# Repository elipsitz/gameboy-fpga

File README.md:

# FPGA Game Boy Emulator

This repository contains a Game Boy / Game Boy Color emulator, written in [Chisel](https://www.chisel-lang.org/), that can be run on an FPGA. Read the full writeup [here](https://eli.lipsitz.net/posts/fpga-gameboy-emulator/).

Currently, only the Pynq-Z2 is supported, although the core of the emulator should be able to be used on any FPGA with sufficient resources.

## Building

A precompiled bitstream is available under Releases.

### Setup

#### Install Vivado

Currently this project uses Vivado 2020.2. The free edition is sufficient. Make sure to install with support for Zynq-7000 SoCs.

Install the [Pynq-Z2 Vivado board files](https://pynq.readthedocs.io/en/latest/overlay_design_methodology/board_settings.html).

Additionally, you should set up a shared IP cache to speed up synthesis of Xilinx IP:
1. Create the `~/vivado_ip_cache` directory (could be located somewhere else).
2. Create the file `~/.Xilinx/Vivado/Vivado_init.tcl`
3. In that file, add `set_param project.defaultIPCacheSetting /home/eli/vivado_ip_cache/` (substituting the absolute path to the IP cache directory).

#### Install other tools

You'll need to install JDK 8 or later, and [Scala Build Tool (`sbt`)](https://www.scala-sbt.org/download.html). Additionally, install [FuseSoC](https://github.com/olofk/fusesoc).

### Building the bitstream

From the top-level directory:

```
fusesoc --cores-root . run --build --target=pynq_z2 elipsitz:gameboy:gameboy
```

This will generate a `.bit` and `.hwh` file, which need to be accessible to the PS Python code.

## Running

### Setup

Install Pynq Linux on the Pynq-Z2, and install the pip packages listed in `python/requirements.txt`.

Transfer the `gameboy_ps` Python module (located in the `python` directory) to the Pynq-Z2.

Place the `gameboy.bit` and `gameboy.hwh` files from the build process in the `gameboy_ps/resources` directory.

### HDMI and Controller

Connect an HDMI cable from the "HDMI OUT" port on the Pynq-Z2 to a monitor or TV.

Attach an Xbox-compatible controller to the USB port of the Pynq-Z2.

### Running 

As root, run `python3 -m gameboy_ps <path to ROM directory>`, passing the path to the directory containing ROM files.

The program will load the bitstream to the PL. It takes a few seconds to load all of the Pynq libraries, but the main menu should soon show up on the display.

Warning: the audio output can be quite loud. Start at the lowest setting on the monitor/TV and increase it as needed.

## Building the cartridge adapter board

To play physical cartridges, you'll need to assemble the adapter board. KiCad board files can be found in the `pcb/pynq_adapter_rev2` directory. The schematic is pre-populated with LCSC part numbers for easy assembly at JLCPCB.

You'll need to add a few components yourself. These are all easy to solder:

* A 2x20 0.1mm female pin header (e.g. [this one](https://www.adafruit.com/product/2222)). These are used for Raspberry Pi HATs, so they're pretty easy to find.
* A SPDT slide switch such as the [EG1218](https://octopart.com/search?q=EG1218), or just a 1x3 strip of 0.1mm male pin header and a jumper.
* A GBA SP slot (such as [this one](https://handheldlegend.com/products/game-boy-cartridge-slot)). These can be found quite cheaply on eBay or Aliexpress as well. They're all pretty much the same.
* If desired, a GBA link port (e.g. [this one](https://handheldlegend.com/products/game-boy-advance-ext-link-port)). These can also be found easily from other sources.

The other parts are relatively small, so I don't recommend hand soldering the board. However, if you want to assemble the whole thing yourself, in addition to assorted resistors and capacitors, you'll also need:

* 6x [74LVC1T45DCK](https://octopart.com/search?q=74LVC1T45DCK) 1-bit level shifters.
* 2x [74LVCH16T245DGGR](https://octopart.com/search?q=74LVCH16T245DGGR) 16-bit level shifters. The non 'H' version should work as well, but the 'H' (bus hold) version is preferable.

## Appendix

### Getting Xbox controller to work on Pynq-Z2

This needs the `xpad` and `joydev` drivers. Pynq Linux isn't built with them. If you're running Pynq Linux with kernel `5.15.19-xilinx-v2022.1`, prebuilt kernel modules can be found in the `extra` directory in the repository. Otherwise, to build loadable kernel modules from scratch:

On the Pynq-Z2, go to `/lib/modules/5.15.19-xilinx-v2022.1/build`.

Download the right version of [`xpad.c`](https://raw.githubusercontent.com/torvalds/linux/v5.15/drivers/input/joystick/xpad.c)
to `drivers/input/joystick/xpad.c`.

And do the same with [`joydev.c`](https://raw.githubusercontent.com/torvalds/linux/v5.15/drivers/input/joydev.c), to `drivers/input/joydev.c`.

The build commands in `/lib/modules` need to run with `sudo` due to permissions issues.

Do `sudo make menuconfig` and set:

* `Device Drivers --> Input device support --> Joystick interface` to `M` (for 'module')
* `Device Drivers --> Input device support --> Joysticks/gamepads --> X-box Gamepad support` to `M` (for 'module')

Save and exit.

Then build the modules:

```
sudo make scripts
sudo make distclean
sudo make prepare
sudo make modules_prepare

sudo make -C . M=drivers/input/ joydev.ko
sudo make -C . M=drivers/input/joystick xpad.ko
```

Install the modules so that they'll be loaded automatically on boot.
Copy the `.ko` files to `/usr/lib/modules/$(uname -r)/kernel/`, and append
to `/etc/modules`:

```
joydev
xpad
```

Alternatively, use `insmod <modules>.ko` to load them once.

Make sure the `xilinx` user is in the group `input`:
`sudo usermod -a -G input xilinx` (and re-login)

Install the Python library with `sudo pip3 install xbox360controller`

Create the device nodes if needed: https://docs.kernel.org/input/joydev/joystick.html#device-nodes

```
cd /dev
rm js*
mkdir input
mknod input/js0 c 13 0
mknod input/js1 c 13 1
mknod input/js2 c 13 2
mknod input/js3 c 13 3
ln -s input/js0 js0
ln -s input/js1 js1
ln -s input/js2 js2
ln -s input/js3 js3
```

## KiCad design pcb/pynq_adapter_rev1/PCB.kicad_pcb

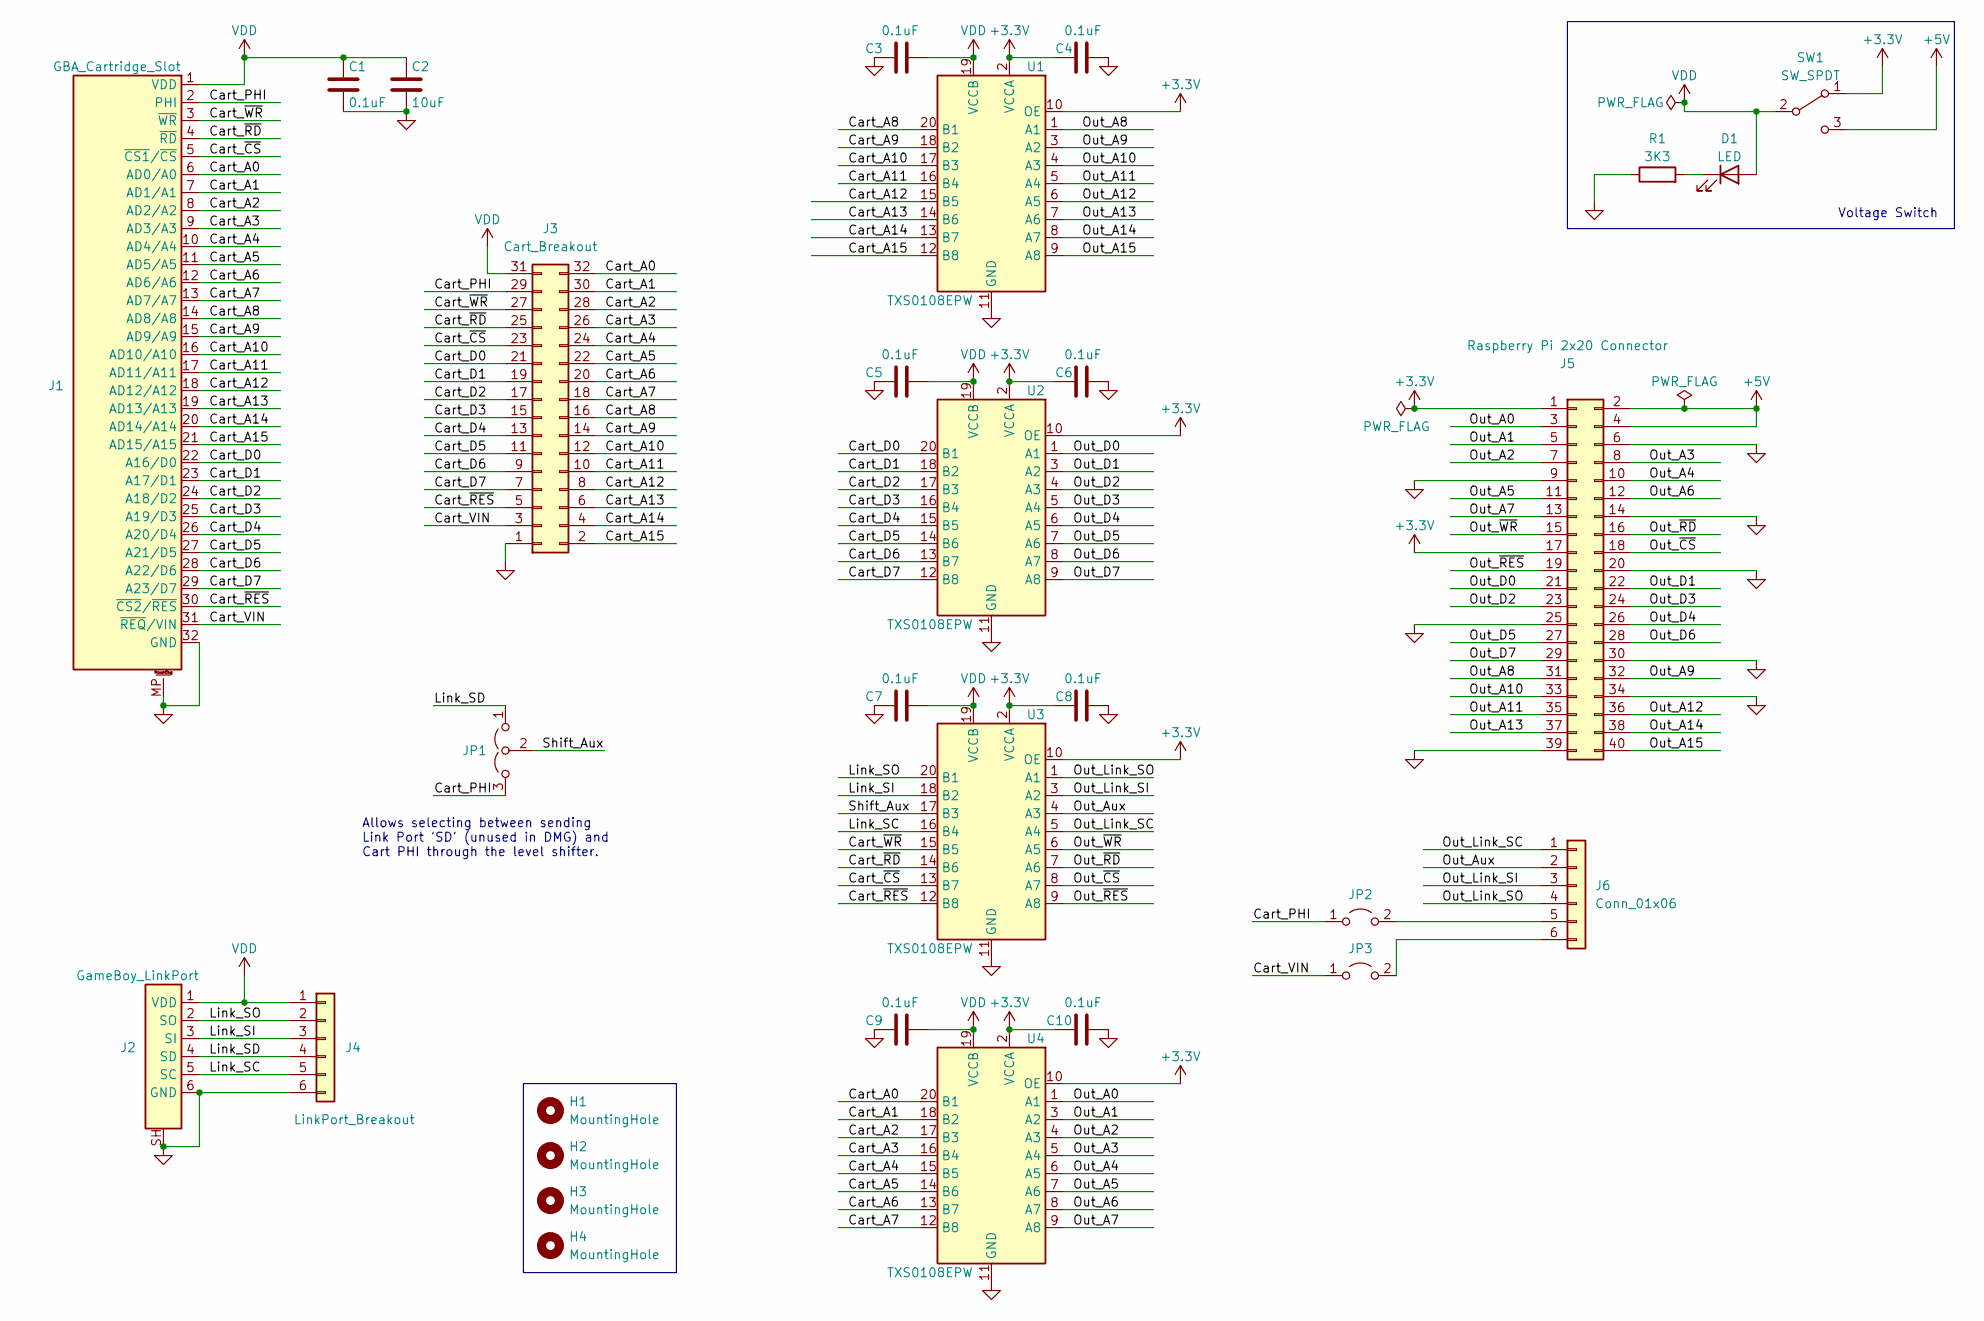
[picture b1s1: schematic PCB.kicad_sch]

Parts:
C1, C3, C4, C5, C6, C7, C8, C9, C10: 0.1uF; C_0603_1608Metric; LCSC C14663
C2: 10uF; C_1206_3216Metric; LCSC C13585
D1: LED; LED_0603_1608Metric; LCSC C2286
H1, H2, H3, H4: MountingHole; MountingHole_3.2mm_M3
J1: GBA_Cartridge_Slot; GameBoy_Cartridge_AGS_1x32-1MP_P1.50mm_Socket_Horizontal
J2: GameBoy_LinkPort; GameBoy_LinkPort_MGB_Horizontal
J3: Cart_Breakout; PinHeader_2x16_P2.54mm_Vertical
J4: LinkPort_Breakout; PinHeader_1x06_P2.54mm_Vertical
J5: Raspberry Pi 2x20 Connector; PinSocket_2x20_P2.54mm_Vertical
J6: Conn_01x06; PinHeader_1x06_P2.54mm_Vertical
JP1: Jumper_3_Open; PinHeader_1x03_P2.54mm_Vertical
JP2, JP3: Jumper_2_Open; PinHeader_1x02_P2.54mm_Vertical
R1: 3K3; R_0402_1005Metric; LCSC C25890
SW1: SW_SPDT; EG1218
U1, U2, U3, U4: TXS0108EPW; TSSOP-20_4.4x6.5mm_P0.65mm

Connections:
+3.3V: C4.2, C6.2, C8.2, C10.2, J5.1 (GND), J5.17 (3V3), SW1.1 (A), U1.2 (VCCA), U1.10 (OE), U2.2 (VCCA), U2.10 (OE), U3.2 (VCCA), U3.10 (OE), U4.2 (VCCA), U4.10 (OE)
+5V: J5.2 (5V), J5.4 (5V), SW1.3 (C)
/Cart_A0: J1.6 (AD0/A0), J3.32, U4.20 (B1)
/Cart_A1: J1.7 (AD1/A1), J3.30, U4.18 (B2)
/Cart_A2: J1.8 (AD2/A2), J3.28, U4.17 (B3)
/Cart_A3: J1.9 (AD3/A3), J3.26, U4.16 (B4)
/Cart_A4: J1.10 (AD4/A4), J3.24, U4.15 (B5)
/Cart_A5: J1.11 (AD5/A5), J3.22, U4.14 (B6)
/Cart_A6: J1.12 (AD6/A6), J3.20, U4.13 (B7)
/Cart_A7: J1.13 (AD7/A7), J3.18, U4.12 (B8)
/Cart_A8: J1.14 (AD8/A8), J3.16, U1.20 (B1)
/Cart_A9: J1.15 (AD9/A9), J3.14, U1.18 (B2)
/Cart_A10: J1.16 (AD10/A10), J3.12, U1.17 (B3)
/Cart_A11: J1.17 (AD11/A11), J3.10, U1.16 (B4)
/Cart_A12: J1.18 (AD12/A12), J3.8, U1.15 (B5)
/Cart_A13: J1.19 (AD13/A13), J3.6, U1.14 (B6)
/Cart_A14: J1.20 (AD14/A14), J3.4, U1.13 (B7)
/Cart_A15: J1.21 (AD15/A15), J3.2, U1.12 (B8)
/Cart_D0: J1.22 (A16/D0), J3.21, U2.20 (B1)
/Cart_D1: J1.23 (A17/D1), J3.19, U2.18 (B2)
/Cart_D2: J1.24 (A18/D2), J3.17, U2.17 (B3)
/Cart_D3: J1.25 (A19/D3), J3.15, U2.16 (B4)
/Cart_D4: J1.26 (A20/D4), J3.13, U2.15 (B5)
/Cart_D5: J1.27 (A21/D5), J3.11, U2.14 (B6)
/Cart_D6: J1.28 (A22/D6), J3.9, U2.13 (B7)
/Cart_D7: J1.29 (A23/D7), J3.7, U2.12 (B8)
/Cart_PHI: J1.2 (PHI), J3.29, JP1.3 (B), JP2.1 (A)
/Cart_VIN: J1.31 (~REQ/VIN), J3.3, JP3.1 (A)
/Cart_~CS: J1.5 (~CS1/~CS), J3.23, U3.13 (B7)
/Cart_~RD: J1.4 (~RD), J3.25, U3.14 (B6)
/Cart_~RES: J1.30 (~CS2/~RES), J3.5, U3.12 (B8)
/Cart_~WR: J1.3 (~WR), J3.27, U3.15 (B5)
/Link_SC: J2.5 (SC), J4.5, U3.16 (B4)
/Link_SD: J2.4 (SD), J4.4, JP1.1 (A)
/Link_SI: J2.3 (SI), J4.3, U3.18 (B2)
/Link_SO: J2.2 (SO), J4.2, U3.20 (B1)
/Out_A0: J5.3 (Zynq_W18), U4.1 (A1)
/Out_A1: J5.5 (Zynq_W19), U4.3 (A2)
/Out_A2: J5.7 (Zynq_V6), U4.4 (A3)
/Out_A3: J5.8 (Zynq_Y18), U4.5 (A4)
/Out_A4: J5.10 (Zynq_Y19), U4.6 (A5)
/Out_A5: J5.11 (Zynq_U7), U4.7 (A6)
/Out_A6: J5.12 (Zynq_C20), U4.8 (A7)
/Out_A7: J5.13 (Zynq_V7), U4.9 (A8)
/Out_A8: J5.31 (Zynq_Y7), U1.1 (A1)
/Out_A9: J5.32 (Zynq_B20), U1.3 (A2)
/Out_A10: J5.33 (Zynq_W8), U1.4 (A3)
/Out_A11: J5.35 (Zynq_Y8), U1.5 (A4)
/Out_A12: J5.36 (Zynq_B19), U1.6 (A5)
/Out_A13: J5.37 (Zynq_W9), U1.7 (A6)
/Out_A14: J5.38 (Zynq_A20), U1.8 (A7)
/Out_A15: J5.40 (Zynq_Y9), U1.9 (A8)
/Out_Aux: J6.2, U3.4 (A3)
/Out_D0: J5.21 (Zynq_V10), U2.1 (A1)
/Out_D1: J5.22 (Zynq_U19), U2.3 (A2)
/Out_D2: J5.23 (Zynq_W10), U2.4 (A3)
/Out_D3: J5.24 (Zynq_F19), U2.5 (A4)
/Out_D4: J5.26 (Zynq_F20), U2.6 (A5)
/Out_D5: J5.27 (Zynq_Y16), U2.7 (A6)
/Out_D6: J5.28 (Zynq_Y17), U2.8 (A7)
/Out_D7: J5.29 (Zynq_Y6), U2.9 (A8)
/Out_Link_SC: J6.1, U3.5 (A4)
/Out_Link_SI: J6.3, U3.3 (A2)
/Out_Link_SO: J6.4, U3.1 (A1)
/Out_~CS: J5.18 (Zynq_U18), U3.8 (A7)
/Out_~RD: J5.16 (Zynq_W6), U3.7 (A6)
/Out_~RES: J5.19 (Zynq_V8), U3.9 (A8)
/Out_~WR: J5.15 (Zynq_U8), U3.6 (A5)
/Shift_Aux: JP1.2 (C), U3.17 (B3)
GND: C1.2, C2.2, C3.1, C4.1, C5.1, C6.1, C7.1, C8.1, C9.1, C10.1, J1.32 (GND), J1.MP, J2.6 (GND), J2.SH, J3.1, J4.6, J5.6 (GND), J5.9 (GND), J5.14 (GND), J5.20 (GND), J5.25 (GND), J5.30 (GND), J5.34 (GND), J5.39 (GND), R1.1, U1.11 (GND), U2.11 (GND), U3.11 (GND), U4.11 (GND)
unnamed: D1.1 (K), R1.2
unnamed: J6.5, JP2.2 (B)
unnamed: J6.6, JP3.2 (B)
VDD: C1.1, C2.1, C3.2, C5.2, C7.2, C9.2, D1.2 (A), J1.1 (VDD), J2.1 (VDD), J3.31, J4.1, SW1.2 (B), U1.19 (VCCB), U2.19 (VCCB), U3.19 (VCCB), U4.19 (VCCB)

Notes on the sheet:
Voltage Switch
Allows selecting between sending Link Port 'SD' (unused in DMG) and Cart PHI through the level shifter.

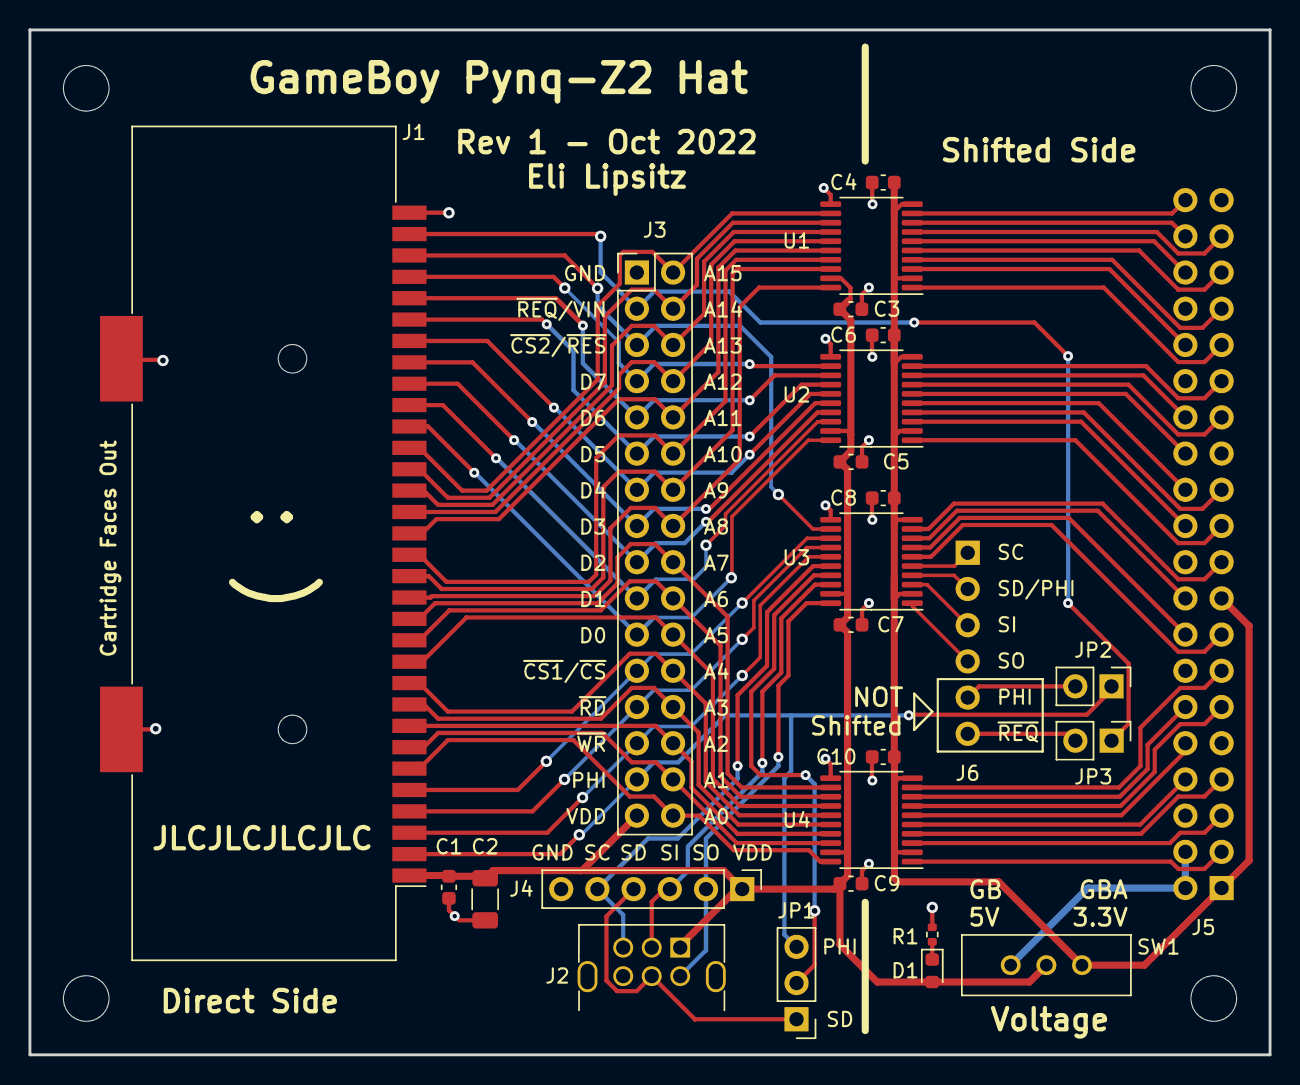
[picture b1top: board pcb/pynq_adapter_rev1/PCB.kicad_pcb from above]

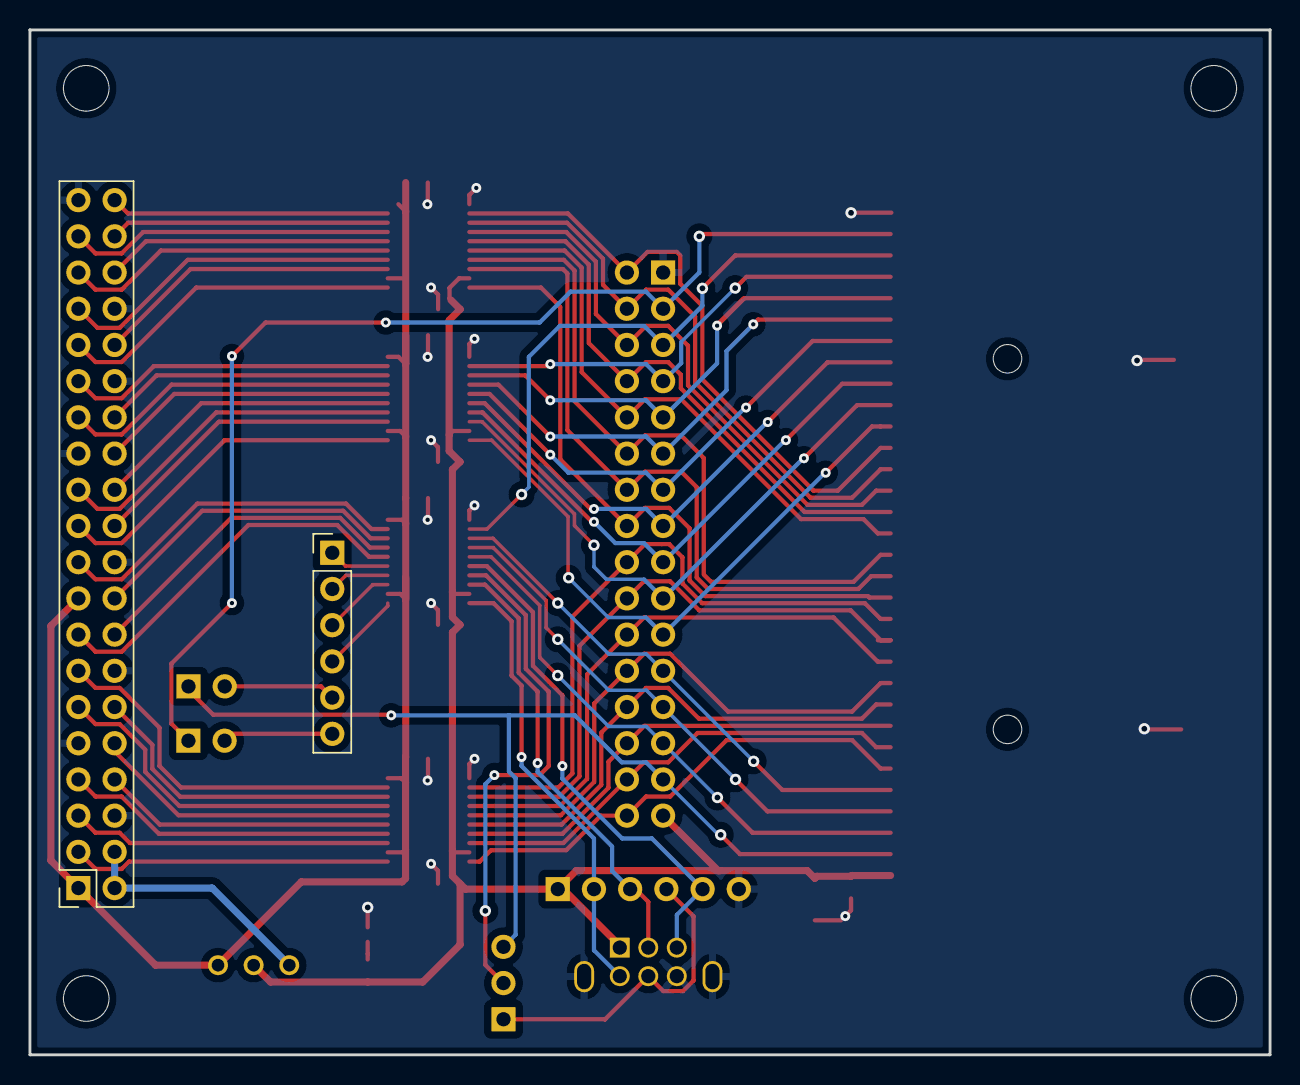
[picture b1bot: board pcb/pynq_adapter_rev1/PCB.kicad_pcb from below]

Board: 2 copper layers, 87.0 x 71.9 mm, 30 parts (2 on the bottom side), 74 nets.

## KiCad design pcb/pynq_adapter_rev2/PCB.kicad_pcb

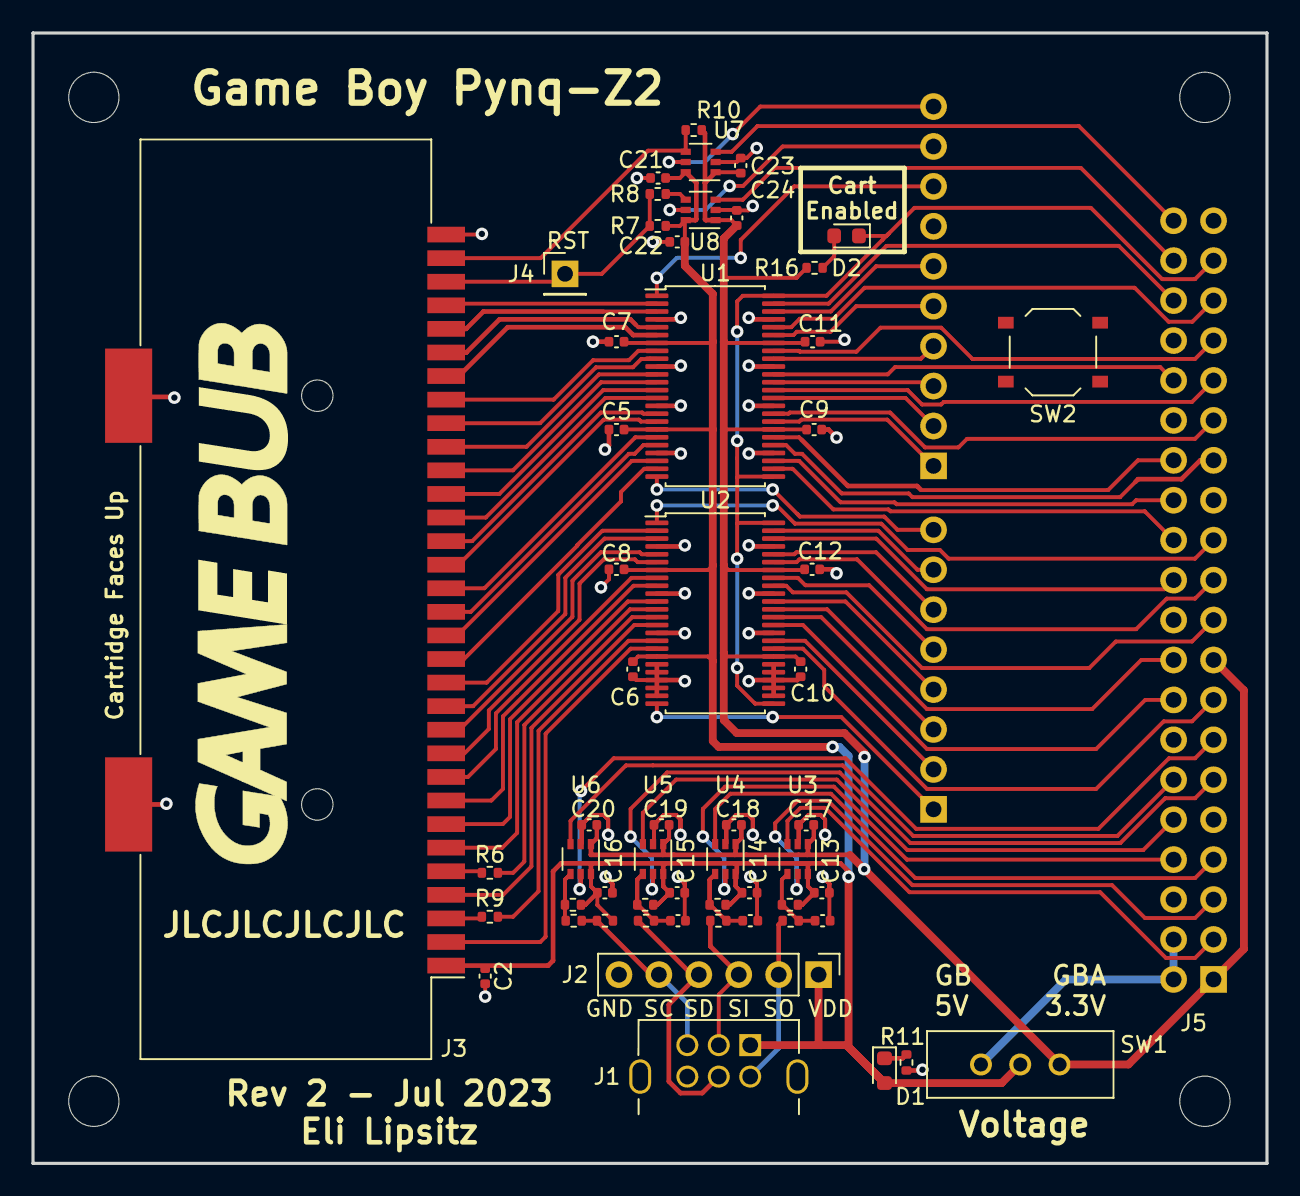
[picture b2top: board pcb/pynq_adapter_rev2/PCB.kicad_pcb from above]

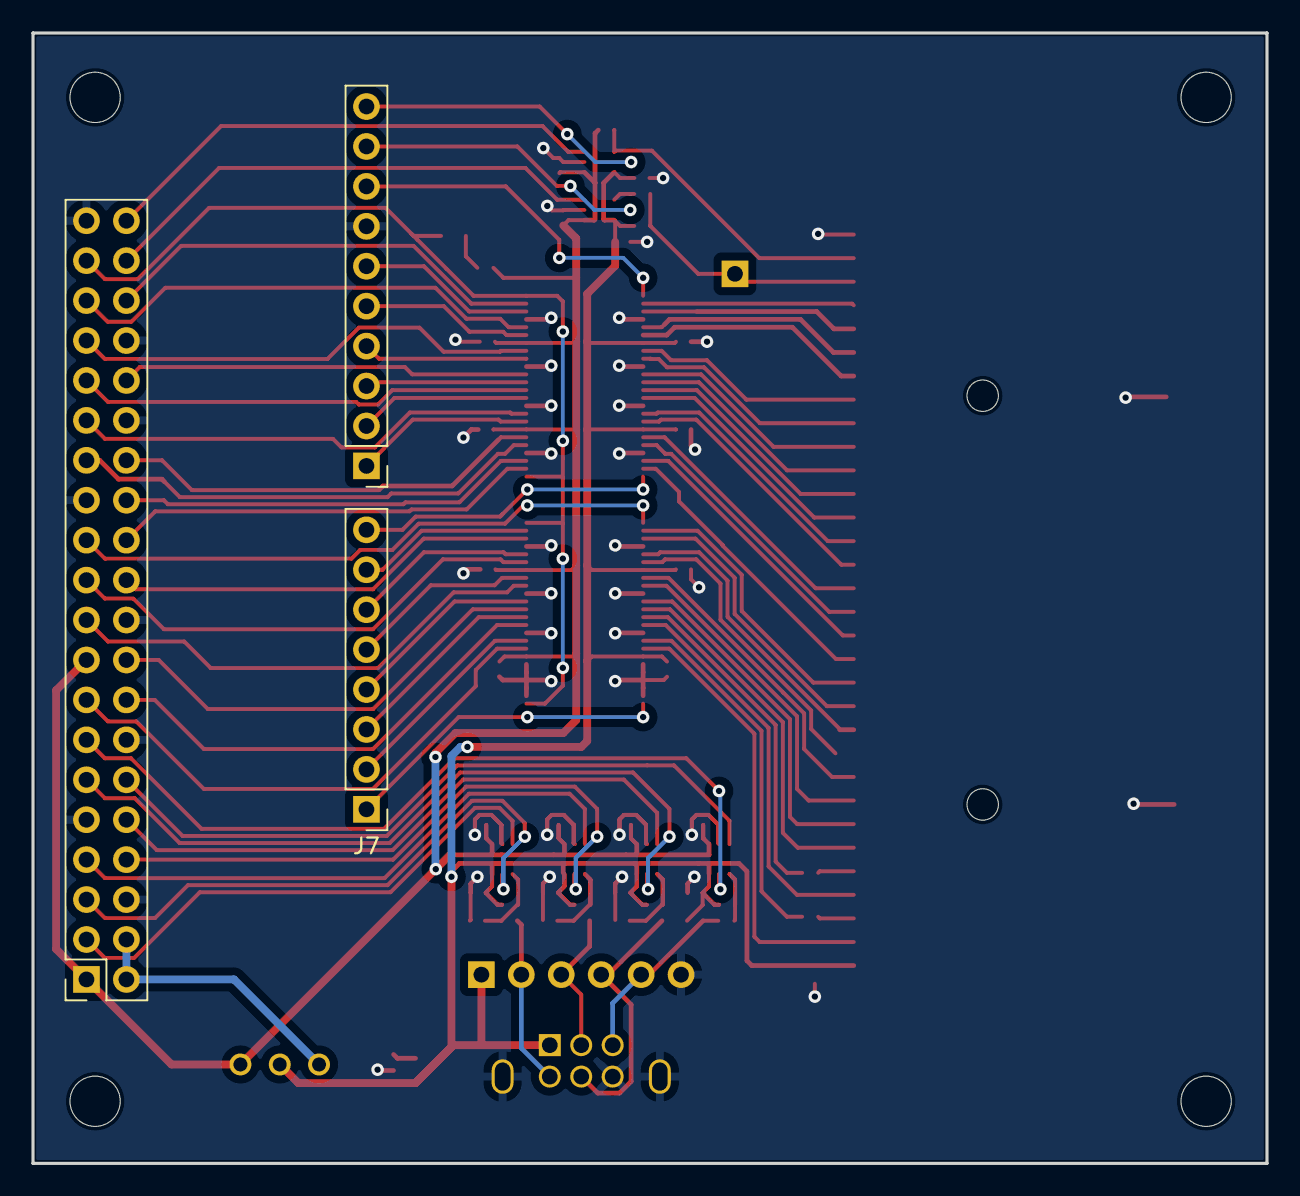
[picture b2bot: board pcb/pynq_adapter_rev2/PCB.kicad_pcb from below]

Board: 2 copper layers, 78.5 x 71.9 mm, 63 parts (3 on the bottom side), 92 nets.

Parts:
C1, C3, C4: 100pF; C_0402_1005Metric
C2, C5, C6, C7, C8, C9, C10, C11, C12, C13, C14, C15, C16, C17, C18, C19, C20, C21, C22, C23, C24: 0.1uF; C_0402_1005Metric
D1, D2: LED; LED_0603_1608Metric
H1, H2, H3, H4: MountingHole; MountingHole_3.2mm_M3
J1: GameBoy_LinkPort; GameBoy_LinkPort_MGB_Horizontal
J2: LinkPort_Breakout; PinHeader_1x06_P2.54mm_Vertical
J3: GBA_Cartridge_Slot; GameBoy_Cartridge_AGS_1x32-1MP_P1.50mm_Socket_Horizontal
J4: Conn_01x01; PinHeader_1x01_P2.54mm_Vertical
J5: Raspberry Pi 2x20 Connector; PinSocket_2x20_P2.54mm_Vertical
J6: Conn_01x10; PinHeader_1x10_P2.54mm_Vertical
J7: Conn_01x08; PinHeader_1x08_P2.54mm_Vertical
R1, R10: 100k; R_0402_1005Metric
R2, R3, R4, R5: 330R; R_0402_1005Metric
R6, R9: 47R; R_0402_1005Metric
R7: 18k; R_0402_1005Metric
R8: 22R; R_0402_1005Metric
R11, R16: 3.3k; R_0402_1005Metric
R12, R13, R14, R15: 10K; R_0402_1005Metric
SW1: SW_SPDT; EG1218
SW2: SW_Push; SW_Push_1P1T_XKB_TS-1187A
U1, U2: SN74LVCH16T245DGGR; TSSOP-48_6.1x12.5mm_P0.5mm
U3, U4, U5, U6, U7, U8: SN74LVC1T45DCKR; SOT-363_SC-70-6

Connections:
+3.3V: C9.2, C10.2, C11.1, C12.1, C17.2, C18.2, C19.2, C20.2, C23.2, C24.2, J5.1 (GND), J5.17 (3V3), R10.2, R16.1, SW1.1 (A), U1.31 (VCCA), U1.42 (VCCA), U2.31 (VCCA), U2.42 (VCCA), U3.1 (VCCA), U4.1 (VCCA), U5.1 (VCCA), U6.1 (VCCA), U7.1 (VCCA), U8.1 (VCCA)
+5V: J5.2 (5V), J5.4 (5V), SW1.3 (C)
Cart_A0: J3.6 (AD0/A0), U2.12 (1B8)
Cart_A1: J3.7 (AD1/A1), U2.11 (1B7)
Cart_A2: J3.8 (AD2/A2), U2.9 (1B6)
Cart_A3: J3.9 (AD3/A3), U2.8 (1B5)
Cart_A4: J3.10 (AD4/A4), U2.6 (1B4)
Cart_A5: J3.11 (AD5/A5), U2.5 (1B3)
Cart_A6: J3.12 (AD6/A6), U2.3 (1B2)
Cart_A7: J3.13 (AD7/A7), U2.2 (1B1)
Cart_A8: J3.14 (AD8/A8), U1.23 (2B8)
Cart_A9: J3.15 (AD9/A9), U1.22 (2B7)
Cart_A10: J3.16 (AD10/A10), U1.20 (2B6)
Cart_A11: J3.17 (AD11/A11), U1.19 (2B5)
Cart_A12: J3.18 (AD12/A12), U1.17 (2B4)
Cart_A13: J3.19 (AD13/A13), U1.16 (2B3)
Cart_A14: J3.20 (AD14/A14), U1.14 (2B2)
Cart_A15: J3.21 (AD15/A15), U1.13 (2B1)
Cart_D0: J3.22 (A16/D0), U1.12 (1B8)
Cart_D1: J3.23 (A17/D1), U1.11 (1B7)
Cart_D2: J3.24 (A18/D2), U1.9 (1B6)
Cart_D3: J3.25 (A19/D3), U1.8 (1B5)
Cart_D4: J3.26 (A20/D4), U1.6 (1B4)
Cart_D5: J3.27 (A21/D5), U1.5 (1B3)
Cart_D6: J3.28 (A22/D6), U1.3 (1B2)
Cart_D7: J3.29 (A23/D7), U1.2 (1B1)
Cart_PHI: J3.2 (PHI), U2.17 (2B4)
Cart_VIN: J3.31 (~REQ/VIN), R10.1, U7.4 (B)
Cart_~CS: R6.2, U2.13 (2B1)
Cart_~RD: J3.4 (~RD), U2.14 (2B2)
Cart_~RES: R8.2, U8.4 (B)
Cart_~WR: R9.2, U2.16 (2B3)
Dir_A_Hi: J7.8, U1.24 (2DIR)
Dir_A_Lo: J5.23 (Zynq_W10), U2.1 (1DIR)
Dir_Ctrl: J7.1, U2.24 (2DIR)
Dir_D: J6.8, U1.1 (1DIR)
Dir_SC: J5.13 (Zynq_V7), U6.5 (DIR)
Dir_SD: J5.11 (Zynq_U7), U5.5 (DIR)
Dir_SI: J5.8 (Zynq_Y18), U4.5 (DIR)
Dir_SO: J5.5 (Zynq_W19), U3.5 (DIR)
Dir_VIN: J6.10, U7.5 (DIR)
Dir_~RES: J6.9, U8.5 (DIR)
GND: C1.2, C2.2, C3.2, C4.2, C5.1, C6.1, C7.2, C8.2, C9.1, C10.1, C11.2, C12.2, C13.1, C14.1, C15.1, C16.1, C17.1, C18.1, C19.1, C20.1, C21.1, C22.1, C23.1, C24.1, J1.6 (GND), J1.SH, J2.6, J3.32 (GND), J3.MP, J5.6 (GND), J5.9 (GND), J5.14 (GND), J5.20 (GND), J5.25 (GND), J5.30 (GND), J5.34 (GND), J5.39 (GND), J6.7, R11.1, U1.4 (GND), U1.10 (GND), U1.15 (GND), U1.21 (GND), U1.28 (GND), U1.34 (GND), U1.39 (GND), U1.45 (GND), U2.4 (GND), U2.10 (GND), U2.15 (GND), U2.19 (2B5), U2.20 (2B6), U2.21 (GND), U2.22 (2B7), U2.23 (2B8), U2.26 (2A8), U2.27 (2A7), U2.28 (GND), U2.29 (2A6), U2.30 (2A5), U2.34 (GND), U2.39 (GND), U2.45 (GND), U3.2 (GND), U4.2 (GND), U5.2 (GND), U6.2 (GND), U7.2 (GND), U8.2 (GND)
Link_SC: R5.2, R15.2, U6.4 (B)
Link_SD: C1.1, R4.2, R14.2, U5.4 (B)
Link_SI: C3.1, R3.2, R13.2, U4.4 (B)
Link_SO: C4.1, R2.2, R12.2, U3.4 (B)
unnamed: D1.1 (K), R11.2
unnamed: D2.2 (A), R16.2
unnamed: J1.5 (SC), J2.5, R1.1, R5.1
unnamed: J1.4 (SD), J2.4, R4.1
unnamed: J1.3 (SI), J2.3, R3.1
unnamed: J1.2 (SO), J2.2, R2.1
unnamed: J3.5 (~CS1/~CS), R6.1
unnamed: J3.30 (~CS2/~RES), J4.1, R7.1, R8.1
unnamed: J3.3 (~WR), R9.1
Out_A0: J5.18 (Zynq_U18), U2.37 (1A8)
Out_A1: J7.4, U2.38 (1A7)
Out_A2: J5.19 (Zynq_V8), U2.40 (1A6)
Out_A3: J7.5, U2.41 (1A5)
Out_A4: J5.21 (Zynq_V10), U2.43 (1A4)
Out_A5: J7.6, U2.44 (1A3)
Out_A6: J5.22 (Zynq_U19), U2.46 (1A2)
Out_A7: J7.7, U2.47 (1A1)
Out_A8: J5.24 (Zynq_F19), U1.26 (2A8)
Out_A9: J5.26 (Zynq_F20), U1.27 (2A7)
Out_A10: J5.27 (Zynq_Y16), U1.29 (2A6)
Out_A11: J5.28 (Zynq_Y17), U1.30 (2A5)
Out_A12: J6.1, U1.32 (2A4)
Out_A13: J5.29 (Zynq_Y6), U1.33 (2A3)
Out_A14: J6.2, U1.35 (2A2)
Out_A15: J5.31 (Zynq_Y7), U1.36 (2A1)
Out_D0: J6.3, U1.37 (1A8)
Out_D1: J5.32 (Zynq_B20), U1.38 (1A7)
Out_D2: J6.4, U1.40 (1A6)
Out_D3: J5.33 (Zynq_W8), U1.41 (1A5)
Out_D4: J6.5, U1.43 (1A4)
Out_D5: J5.35 (Zynq_Y8), U1.44 (1A3)
Out_D6: J6.6, U1.46 (1A2)
Out_D7: J5.36 (Zynq_B19), U1.47 (1A1)
Out_PHI: J5.15 (Zynq_U8), U2.32 (2A4)
Out_SC: J5.12 (Zynq_C20), U6.3 (A)
Out_SD: J5.10 (Zynq_Y19), U5.3 (A)
Out_SI: J5.7 (Zynq_V6), U4.3 (A)
Out_SO: J5.3 (Zynq_W18), U3.3 (A)
Out_VIN: J5.40 (Zynq_Y9), U7.3 (A)
Out_~CS: J7.3, U2.36 (2A1)
Out_~RD: J5.16 (Zynq_W6), U2.35 (2A2)
Out_~RES: J5.38 (Zynq_A20), U8.3 (A)
Out_~WR: J7.2, U2.33 (2A3)
VDD: C2.1, C5.2, C6.2, C7.1, C8.1, C13.2, C14.2, C15.2, C16.2, C21.2, C22.2, D1.2 (A), J1.1 (VDD), J2.1, J3.1 (VDD), R1.2, R7.2, R12.1, R13.1, R14.1, R15.1, SW1.2 (B), U1.7 (VCCB), U1.18 (VCCB), U2.7 (VCCB), U2.18 (VCCB), U3.6 (VCCB), U4.6 (VCCB), U5.6 (VCCB), U6.6 (VCCB), U7.6 (VCCB), U8.6 (VCCB)
~OE: D2.1 (K), J5.37 (Zynq_W9), U1.25 (2~OE), U1.48 (1~OE), U2.25 (2~OE), U2.48 (1~OE)

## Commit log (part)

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2022-02-05 Stub out cpu module with cocotb testbench
2022-02-05 Add top level Makefile, use cocotb clock helper
2022-02-05 Stub out CPU control unit and m-cycle clocking
2022-02-07 Initial microcode generation and state machine
2022-02-07 Add basic program execution in testbench
2022-02-09 Add initial register file, implement 'load immediate to reg8' to test it
2022-02-09 Speed up control state transition by dispatching directly from memory in
2022-02-10 Implement load to/from (HL) instructions
2022-02-10 Refactor register writing to use RegOp to support HL+ and HL-
2022-02-10 Add temp registers, implement LD (HL),n
2022-02-11 Add ability to assemble ROMs with RGBDS and run them
2022-02-11 Implement 16-bit immediate load, inc/dec HL/A loads
2022-02-11 Implement ALU A,r and ALU A,(HL) instructions
2022-02-12 Implement JP nn
2022-02-12 Implement JP with condition
2022-02-12 Add basic sanity test
2022-02-12 Add more stuff to the complete tests
2022-02-13 Refactor ALU operations to always have Op1=A
2022-02-13 Implement LD (rr), A and LD A, (rr)
2022-02-13 Implement LDH instructions
2022-02-13 Refactor to have an incrementer/decrementer address calculation unit
2022-02-13 Implement 'LD (nn), SP'
2022-02-13 Remove some redundant states
2022-02-14 Implement PUSH/POP (for registers other than AF)
2022-02-15 Refactor PC increment to use incrementer
2022-02-15 Reduce warnings in test Python
2022-02-15 Move PC into register file
2022-02-17 Refactor ALU into a separate module with unified opcodes
2022-02-17 Implement 16-bit signed adds (with SP and HL)
2022-02-18 Implement PUSH/POP AF
2022-02-18 Implement conditional JR
2022-02-18 Implement CALL/RET (conditional and regular)
2022-02-21 Implement unary accumulator/flag ops (except DAA)
2022-02-21 Implement dispatch for CB-prefixed instructions
2022-02-21 Implement CB-prefixed single-bit operations
2022-02-21 Implement EI/DI
2022-02-21 Implement RETI
2022-02-26 Implement RST
2022-02-26 Fix some Verilator warnings
2022-02-26 Add Verilator harness to run ROMs
2022-03-01 Fix a flags bug, and initialize CPU state to after bootrom
2022-03-01 Very hacky CPU testing with gbit
    From https://github.com/koenk/gbit
    Also needs the `lib` folder put into /sim/
    Also needs the libgbit.so compiled and put into /sim/
2022-03-01 Sort of implement STOP instruction
2022-04-08 Eliminate Verilator warnings
2022-04-09 Initial effort to create gameboy module
2022-04-10 Switch CPU mem_enable to only happen for one t-cycle
2022-04-10 Allow using 'make sim' in top level directory to make rtl and simulator
2022-04-13 Refactor simulator into a separate class
2022-04-13 Add SDL window rendering
2022-04-13 Stub out PPU pixel output interface
2022-04-18 Keep track of scanlines and cycles
2023-04-01 Add Chisel template
2023-04-03 Add Chisel CPU
2023-04-03 Add CPU test harness -- basic tests passing
2023-04-04 cpu: Fix Flags bundle ordering
2023-04-04 Finish CPU tests, all pass
2023-04-04 Add Gameboy module with basic memory for simulation
2023-04-04 Always rebuild rtl in Makefile
2023-04-04 Fix memory enable signal
2023-04-05 Emit verilog for TestableCpu
2023-04-05 Expose instruction load control signal in TestableCpu
2023-04-05 Fix ALU operands for CB instructions
2023-04-07 cpu: Add internal IE/IF registers
2023-04-07 cpu: Start implementing interrupts (not working)
2023-04-08 cpu: Start PC at 0x0100
2023-04-13 Refactor peripherals
2023-04-13 cpu: Add HALT tests to interrupt tests
2023-04-13 Making timer work with blargg test
2023-04-13 Refactor peripheral bus to use Mux1H
2023-04-13 cpu: Exit from halt on interrupt
2023-04-13 Refactor external bus, work ram to use single port ram
2023-04-13 Add vram and oam
2023-04-13 ppu: Create PPU, link output with simulator
2023-04-13 ppu: Add interrupts
2023-04-13 ppu: Add state tracking and transitions
2023-04-13 ppu: Display first tiledata on screen
2023-04-14 ppu: Initial background drawing (needs to be cleaned up)
2023-04-14 ppu: Simplify PixelFifo and fetcher logic
2023-04-14 ppu: Use background palette
2023-04-15 ppu: Implement window
2023-04-15 ppu: Implement oam search
2023-04-15 ppu: Start working on obj fetch and fifo
2023-04-16 ppu: Fix pixel pusher not waiting for obj fetch
2023-04-16 ppu: Fix incorrect obj palette
2023-04-16 ppu: Fix obj/bg priority bit
2023-04-16 ppu: Merge incoming obj pixels with existing fifo contents
2023-04-16 ppu: respect obj enable bit
2023-04-16 Implement OAM dma
2023-04-16 simulator: Add pause with cmd-P
2023-04-16 joypad: Implement joypad
2023-04-17 gb: Implement boot rom
2023-04-17 joypad: Implement IRQ
2023-04-17 ppu: Fix sprite overlap causing horizontal flipping
2023-04-18 sim: Start making cartridge mappers
2023-04-18 sim: Implement MBC1
2023-04-18 ppu: Fix window being invisible when WX < 8
2023-04-18 sim: Fix reading/writing to ram in mbc3 (and mbc1)
2023-04-19 ppu: Reset sprite fifo between scanlines
2023-04-19 sim: Support MBC5
2023-04-19 ppu: Draw first 8 pixels in scanline (hidden)
2023-04-25 ppu: Better handling of PPU disabled
    NOTE: Metroid scrolling has a weird artifact / tearing
2023-04-25 sim: Switch to double buffering to prevent tearing
2023-04-25 sim: Initialize SDL audio
2023-04-25 sim: Add Audio::push
2023-04-26 sim: Sample APU and output audio
2023-04-26 sim: Add single stepping
2023-04-26 cpu: Switch control table and dispatch table to use a ROM for Verilator performance
2023-04-26 apu: Stub out global and channel 1 registers
2023-04-26 apu: Mixer and volume output
2023-04-27 apu: Work on channel 1 duty and envelope
2023-04-27 sim: Reinterpret audio samples as signed 10-bit audio
2023-04-28 apu: Create dedicated VolumeEnvelope module
2023-04-28 apu: Refactor into separate FrameSequencer module
2023-04-28 Apu: Move volume and length modules into pulse chanel
2023-04-28 apu: NR52 bits don't depend on DAC enable
2023-04-28 apu: Move frequency sweep into pulse channel
2023-04-28 apu: Stub out wave ram
2023-04-28 apu: Most of wave channel, without reading ram
2023-04-29 apu: Stub out channel 4 with registers
2023-04-29 apu: Implement noise channel LFSR
2023-04-29 apu: Fix noise channel length control size
2023-04-29 sim: Bump audio amplitude by 8x
2023-04-29 apu: pass blargg test 01-registers
2023-04-29 gameboy: Enable ppu and apu if skipping bootrom
2023-04-30 ppu: Add hack workaround for LY=153 bug
2023-04-30 cpu: Remove unused imports from TestableCpu
2023-04-30 util: Extract some utilities
2023-04-30 pynq-z2: Add base constraints file
2023-04-30 pynq-z2: Add test counter with fusesoc
2023-05-01 pynq-z2: Get audio working over HDMI
2023-05-01 pynq-z2: Improve audio output, allow turning off via switch and tone via buttons
2023-05-05 sim: Add cmd-R to reset
2023-05-05 build: Make fusesoc use Chisel as a generator
2023-05-05 gameboy: Add 'optimizeForSimulation' parameter, apply to MemRomTable
2023-05-06 build: Test Pynq overlay
2023-05-07 zynq: Switch to HP0 port, add AXI3->AXI4-Lite converter
2023-05-08 Use Zynq PS in pynq-z2 top, along with joypad support via xpad
2023-05-08 build: Specify sbt main class in generator
2023-05-08 Add basic, read-only AxiLiteInitiator
2023-05-09 Test out the AxiLiteInitiator with Pynq
    It works, but doesn't quite access memory correctly.
    It's as though all reads (which are 32-bit) are forcibly 64-bit aligned.
    So two successive 32-bit reads read the same thing, then the next jumps
    up by 8 bytes.
    This seems to be an issue with the AXI_HP0 port. If I switch it to the
    AXI_GP0 port it works fine (with maybe a cycle more of latency?).
2023-05-09 Switch to using HP_AXI in 64-bit mode directly
2023-05-11 Switch to ZynqGameboy, add registers to see CPU state and pause gameboy
2023-05-12 gb: Make ZynqGameboy read ROM from DRAM over AXI (no MMC)
2023-05-12 Start making emulated cartridge for simulator
2023-05-12 Make EmuCartridge more reusable
2023-05-12 Implement MBC1
2023-05-12 Implement emulated cartridge for ZynqGameboy
    MBC1 seems to work with Metroid (with some issues...) but not Zelda.
    Might be because RAM isn't writable at all yet.
    Although Vivado says the design couldn't meet timing.
2023-05-13 Implement writing to RAM in ZynqGameboy
2023-05-13 Implement emulated MBC3
2023-05-13 Persist save file on Pynq-Z2
2023-05-13 Start implementing Serial
2023-05-15 Implement Serial for ZynqGameboy
    Note that this doesn't quite work with the TXS0108B. The serial output
    when a cable isn't connected is correct, but when a cable is connected
    the capacitance (presumably) throws things off and makes the outputs
    oscillate and not be usable.
    Directly connecting the Pynq-Z2 pins seems to work some of the time.
    Presumably a better circuit would be better, maybe just open drain using
2023-05-15 Add PLL locked, regenerate Zynq PS Tcl
2023-05-16 Center gameboy in HDMI output, don't repeat it
2023-05-16 ppu: Don't activate window until we're done fetching objects
    This fixes an issue in Pokemon Gold where the cursor (sprites)
    in the Pokedex's list of Pokemon (a window) would shift the
    window forward by one pixel, when the WX was exactly equal
    to the X position (in OAM) of a sprite
2023-05-17 Rework clocking in ZynqGameboy to address timing issues
    Previously, there were several asynchronous clocks:
    * 100 MHz clock from PS, used to clock AXI target and initiator
    and as the input clock to the PLL:
    * ~ 8 MHz clock used to make the gameboy clock
    * The 25.2 and 126 MHz clocks used for HDMI output
    There were lots of CDC issues between:
2023-05-19 Handle framebuffer within ZynqGameboy
2023-06-10 Allow Zynq PS to update framebuffer
2023-06-10 Expose PS i2c-0 to PMOD B via EMIO
2023-06-11 python: Refactor controller support
2023-06-11 python: Add support for Wii Classic Controller
2023-06-11 Allow switching between emulated and physical cartridge in same bitstream
2023-06-11 Allow resetting ZynqGameboy via MMIO register
2023-06-12 Output 15-bit color from ZynqGameboy
2023-06-13 ** start working on framebuffer blit
2023-06-30 Add copy framebuffer method
2023-06-30 Update framebuffer copy to work with Pillow's I mode instead of I;16
2023-07-01 Add System wrapper
2023-07-01 Add basic UI system
2023-07-01 Add basic main menu
2023-07-01 Add ROM select menu
2023-07-01 Persist battery-backed RAM when in-game menu is opened
2023-07-02 Implement MBC3 RTC
2023-07-02 Implement RtcAccess for ZynqGameboy
2023-07-03 Update RTC based on system time elapsed when loading game
2023-07-03 Implement MBC2
2023-07-03 Add error modal in ROM load screen
2023-07-07 Add xbox home button
2023-07-07 Let ROM list wrap around from top to bottom
2023-07-09 Fix some clocker-related issues
2023-07-09 Add DMG/CGB model compile option and CGB bootrom
2023-07-10 Add support for 4mhz/8mhz input clocks in Clocker
2023-07-10 Refactor some system control registers to SystemControl module
2023-07-10 Handle vram/wram banking
2023-07-10 Load bg tile attributes in CGB mode
2023-07-10 Support VRAM bank attribute in CGB mode
2023-07-10 CGB obj vs obj index priority
2023-07-10 Output 15-bit color from PPU
2023-07-10 Fix incorrect tile data for some BG tiles in CGB mode
2023-07-10 Remove padding in the middle of CGB-style bootroms
2023-07-10 CGB: only overwrite obj pixels if new pixel is opaque
2023-07-11 Implement double-speed mode
2023-07-12 Add basic cartridge access bitstream
2023-07-14 Fix link cable
2023-07-14 Only enable physical cartridge OE if not using emu cart
2023-07-15 Implement CGB fast serial (not tested)
2023-07-15 README: Add notes about running fusesoc and setting up Vivado IP cache
2023-07-16 Add cache in front of DRAM
2023-07-16 Switch SimpleCache to use memory instead of registers, make it bigger
2023-07-16 Add CGB-only APU digital output registers
2023-07-17 Implement CGB VRAM DMA
2023-07-17 update gitignore
2023-07-19 Blank Zynq framebuffer when LCD is off
2023-07-19 Organize the ZynqGameboy registers into groups
2023-07-19 Add basic stats display (with # clocks overflow issues)
2023-07-19 Remember last position in rom select list
2023-07-23 Add Jupyter notebook dealing with reading from GBA cartridges
2023-07-23 Don't poll I2C controller so frequently upon failure
2023-07-23 Fix bug where a series of HALTs would skip through all of them on an interrupt
2023-07-23 Fix rom select list position memory
2023-08-02 Note the property needed in XDC to enable bitstream compression
2023-09-27 Add license

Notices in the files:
parts and their libraries:
Copyright 2021 Accelerated Designs. All rights reserved.
